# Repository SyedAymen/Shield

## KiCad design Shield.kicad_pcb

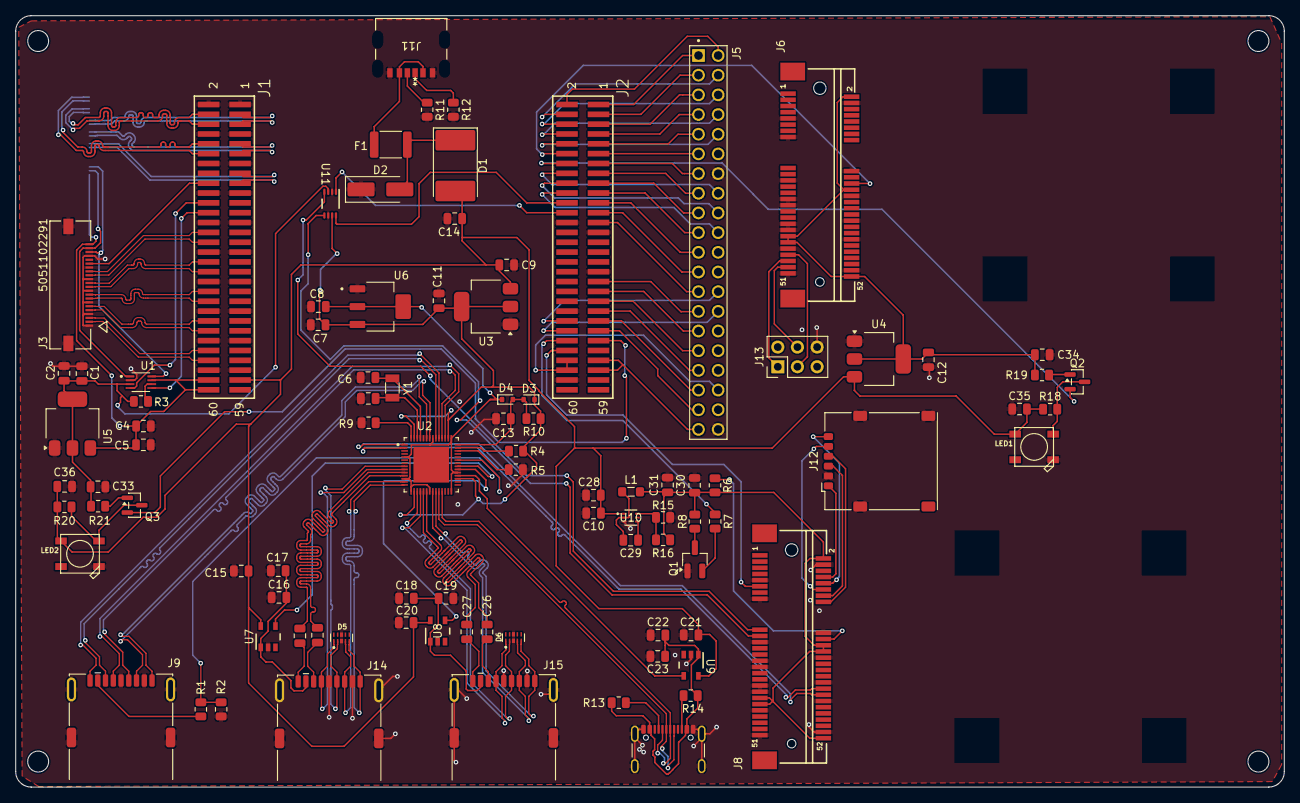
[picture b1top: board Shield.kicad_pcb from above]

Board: 4 copper layers, 163.7 x 99.6 mm, 94 parts (1 on the bottom side), 138 nets.

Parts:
C1, C4: 4.7 u; C_0805_2012Metric
C2, C5, C13, C15, C16, C18, C20, C21, C22, C24, C25, C26, C27, C29, C33, C34, C35, C36: 0.1 u; C_0805_2012Metric
C3, C6: 22 p; C_0805_2012Metric
C7, C9, C10, C14, C28: 10 u; C_0805_2012Metric
C8, C11, C12, C30, C31: 22 u; C_0805_2012Metric
C17, C19, C23: 100 u; C_0805_2012Metric
D1: D_Schottky; D_3220_8050Metric_Pad2.65x5.15mm_HandSolder
D2: D_TVS; D_SMA_Handsoldering
D3, D4: 1N4148WT; D_SOD-523
D5, D6: TPD4E02B04DQAR; DIO_TPD4E02B04DQAR
F1: Polyfuse; Fuse_1812_4532Metric
J1, J2: SAMTEC-FTS-130-01-X-DV
J3, J4: 5051102291; CON_5051102291_MOL
J5: 77313-118-40LF; AMPHENOL_77313-118-40LF
J6, J8: Bus_PCI_Express_Mini; TE_1775862-2
J7: USB_C_Receptacle; USB_C_Receptacle_GCT_USB4105-xx-A_16P_TopMnt_Horizontal
J9, J14, J15: USB3_A; USB_A_Receptacle_XKB_U231-091N-4BLRA00-S
J11: USB_C_Receptacle_PowerOnly_6P; U262-061N-4BVC10_XKB
J12: SIM_Card_Shielded; nanoSIM_Hinged_CUI_NSIM-2-C
J13: Conn_02x03_Odd_Even; PinHeader_2x03_P2.54mm_Vertical
L1: 3.3 uH; L_0805_2012Metric_Pad1.05x1.20mm_HandSolder
LED1, LED2: WS2812B
Q1: 2N3904; SOT-23_Handsoldering
Q2, Q3: MMBT3904; SOT-23
R1, R2, R6: 100 K; R_0805_2012Metric
R3, R7, R8, R15: 10 K; R_0805_2012Metric
R4: 200 K; R_0805_2012Metric
R5: 10; R_0805_2012Metric
R9, R10: 12 K; R_0805_2012Metric
R11, R12: 5.1 K; R_0805_2012Metric
R13, R14: 56 K; R_0805_2012Metric
R16: 33 K; R_0805_2012Metric
R18, R20, R21: 1 K; R_0805_2012Metric
R19: 2.2 K; R_0805_2012Metric
U1: TCA9406DCUR; SOP50P310X90-8N
U2: USB5744_2G; QFN40P700X700X100-57N
U3, U4: AMS1117-3.3; SOT-223-3_TabPin2
U5: AMS1117-1.8; SOT-223-3_TabPin2
U6: LM1117S-1.2; SOT230P695X180-4N
U7, U8, U9: TPS2051BDBVR; DBV0005A_N
U10: AP62300Z6-7; SOT563-Z6_1_DIO
U11: TXB0102DCUR; DCU0008A_N
Y1: Crystal; Crystal_SMD_3215-2Pin_3.2x1.5mm

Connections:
/1V8: C1.2, C2.2, C33.2, R3.1, R21.2, U1.3 (VCCA), U5.2 (VO), U11.3 (VCCA)
/3V3: C4.2, C5.2, J1.58, J1.60, J3.22, J4.22, U1.7 (VCCB), U5.3 (VI)
/3V3-VBUS-2: C12.2, C34.2, J6.2 (+3V3AUX), J6.24 (+3V3AUX), J6.39 (+3V3AUX), J6.41 (+3V3AUX), J6.52 (+3V3AUX), R19.1, U4.2 (VO)
/5V-VBUS: C9.2, C10.2, C14.2, C15.2, C20.2, C21.2, C28.2, C35.2, C36.2, D1.2 (A), J1.57, LED1.1-VDD (VDD), LED2.1-VDD (VDD), R18.1, R20.2, U3.3 (VI), U4.3 (VI), U7.5 (IN), U8.5 (IN), U9.5 (IN), U10.1 (VIN)
/5V-VBUS-PRT-2: C16.2, C17.2, J14.1 (VBUS), U7.1 (OUT)
/5V-VBUS-PRT-3: C18.2, C19.2, J15.1 (VBUS), U8.1 (OUT)
/5V-VBUS-PRT-4: C22.2, C23.2, J7.A4 (VBUS), J7.A9 (VBUS), J7.B4 (VBUS), J7.B9 (VBUS), R13.1, R14.1, U9.1 (OUT)
/CAM_EN: J1.18, J3.17
/CSI_CK+: J1.40, J3.9
/CSI_CK-: J1.42, J3.8
/CSI_D0+: J1.52, J3.3
/CSI_D0-: J1.54, J3.2
/CSI_D1+: J1.46, J3.6
/CSI_D1-: J1.48, J3.5
/CSI_D2+: J1.34, J3.12
/CSI_D2-: J1.36, J3.11
/CSI_D3+: J1.28, J3.15
/CSI_D3-: J1.30, J3.14
/DN2_D+: D5.2 (IO2), J14.3 (D+), U2.8 (USB2DN_DP2/PRT_DIS_P2)
/DN2_D-: D5.1 (IO1), J14.2 (D-), U2.9 (USB2DN_DM2/PRT_DIS_M2)
/DN2_RX+: D5.4 (IO3), J14.6 (SSRX+), U2.13 (USB3DN_RXDP2)
/DN2_RX-: D5.5 (IO4), J14.5 (SSRX-), U2.14 (USB3DN_RXDM2)
/DN2_TX1+: C25.2, J14.8 (SSTX-)
/DN2_TX1-: C24.2, J14.9 (SSTX+)
/DN2_TX+: C24.1, U2.10 (USB3DN_TXDP2)
/DN2_TX-: C25.1, U2.11 (USB3DN_TXDM2)
/DN3_D+: D6.2 (IO2), J15.3 (D+), U2.17 (USB2DN_DP3/PRT_DIS_P3)
/DN3_D-: D6.1 (IO1), J15.2 (D-), U2.18 (USB2DN_DM3/PRT_DIS_M3)
/DN3_RX+: D6.4 (IO3), J15.6 (SSRX+), U2.22 (USB3DN_RXDP3)
/DN3_RX-: D6.5 (IO4), J15.5 (SSRX-), U2.23 (USB3DN_RXDM3)
/DN3_TX1+: C26.2, J15.8 (SSTX-)
/DN3_TX1-: C27.2, J15.9 (SSTX+)
/DN3_TX+: C27.1, U2.19 (USB3DN_TXDP3)
/DN3_TX-: C26.1, U2.20 (USB3DN_TXDM3)
/DN4_D+: J7.A6 (D+), J7.B6 (D+), U2.24 (USB2DN_DP4/PRT_DIS_P4)
/DN4_D-: J7.A7 (D-), J7.B7 (D-), U2.25 (USB2DN_DM4/PRT_DIS_M4)
/DSI_CK+: J1.5, J4.9
/DSI_CK-: J1.3, J4.8
/DSI_D0+: J1.10, J4.3
/DSI_D0-: J1.12, J4.2
/DSI_D1+: J1.4, J4.6
/DSI_D1-: J1.6, J4.5
/DSI_D2+: J1.11, J4.12
/DSI_D2-: J1.9, J4.11
/DSI_D3+: J1.17, J4.15
/DSI_D3-: J1.15, J4.14
/JOUT_3V3: J2.53, J2.55, J5.39
/JOUT_5V: J2.54, J2.56, J5.36
/LR_MISO: J6.47 (Reserved), J13.1
/LR_MOSI: J6.49 (Reserved), J13.4
/LR_SCK: J6.45 (Reserved), J13.3
/LTE_D+: J8.38 (USB_D+), U2.1 (USB2DN_DP1/PRT_DIS_P1)
/LTE_D-: J8.36 (USB_D-), U2.2 (USB2DN_DM1/PRT_DIS_M1)
/LTE_UART_RXD: J8.19 (UIM_C4), U11.5 (A1)
/LTE_UART_TXD: J8.17 (UIM_C8), U11.4 (A2)
/MCU_CRS_SYNC / PA10: J2.25, J5.25
/MCU_I2C4_SCL / PF14: J2.16, J5.16
/MCU_I2C4_SDA / PF15: J2.18, J5.18
/MCU_MCO / PA8: J2.23, J5.23
/MCU_OPAMP1_VOUT / PA3: J2.20, J5.20
/MCU_PA0 UART4_TX AF8: J2.22, U11.8 (B1)
/MCU_PA1 UART4_RX AF8: J2.24, U11.1 (B2)
/MCU_PE7_LR: J2.12, J6.22 (~PERST)
/MCU_PE8_LED: J2.14, Q2.2 (E)
/MCU_PSSI_D0 / PC6: J2.1, J5.01
/MCU_PSSI_D1 / PC7: J2.3, J5.03
/MCU_PSSI_D2 / PC8: J2.5, J5.05
/MCU_PSSI_D3 / PC9: J2.7, J5.07
/MCU_PSSI_D4 / PE4: J2.9, J5.09
/MCU_PSSI_D5 / PI4: J2.11, J5.11
/MCU_PSSI_D6 / PI6: J2.13, J5.13
/MCU_PSSI_D7 / PI7: J2.15, J5.15
/MCU_PSSI_DE / PD8: J2.21, J5.21
/MCU_PSSI_PDCK / PD9: J2.17, J5.17
/MCU_PSSI_RDY / PI5: J2.19, J5.19
/MCU_SDMMC1_CMD / PD2: J2.2, J5.02
/MCU_TRACE_CLK / PE2: J2.4, J5.04
/MCU_TRACE_D0 / PE3: J2.6, J5.06
/MCU_TRACE_D2 / PE5: J2.8, J5.08
/MCU_TRACE_D3 / PE6: J2.10, J5.10
/PRT_CTL2: U2.35 (PRT_CTL2), U7.4 (EN)
/PRT_CTL3: U2.34 (PRT_CTL3), U8.4 (EN)
/PRT_CTL4: U2.32 (PRT_CTL4/GANG_PWR), U9.4 (EN)
/RST: C13.2, D3.2 (A), D4.2 (A), R10.2, U2.42 (RESET_N)
/SCL: J1.24, U1.5 (SCL_A)
/SCL1: J3.20, J4.20, U1.8 (SCL_B)
/SDA: J1.22, U1.4 (SDA_A)
/SDA1: J3.21, J4.21, U1.1 (SDA_B)
/SIM_CLK: J8.12 (UIM_CLK), J12.3 (CLK)
/SIM_DT: J8.10 (UIM_DATA), J12.7 (I/O)
/SIM_RST: J8.14 (~UIM_RESET), J12.2 (RST)
/SIM_VCC: J8.8 (UIM_PWR), J12.1 (VCC)
/SIM_VPP: J8.16 (UIM_VPP), J12.6 (VPP)
/SOC_GPIO_0_SE0: J2.37, J5.27
/SOC_GPIO_1_SEO: J2.39, J5.29
/SOC_GPIO_2_SEO: J2.41, J5.31
/SOC_GPIO_3_SEO: J2.43, J5.33
/SOC_GPIO_18_PWM_LED: J2.49, Q3.2 (E)
/SOC_GPIO_82_SEO: J2.47, J5.37
/SOC_GPIO_86_SEO: J2.45, J5.35
/SOC_GPIO_98: J2.46, J5.26
/SOC_GPIO_99: J2.48, J5.28
/SOC_GPIO_100_PRST_LTE: J2.50, R7.2
/SOC_GPIO_101_PPS: J2.52, J8.11 (REFCLK-)
/UP_D+: J9.3 (D+), U2.46 (USB2UP_DM)
/UP_D-: J9.2 (D-), U2.45 (USB2UP_DP)
/UP_RX+: J9.6 (SSRX+), U2.50 (USB3UP_RXDP)
/UP_RX-: J9.5 (SSRX-), U2.51 (USB3UP_RXDM)
/UP_TX+: J9.9 (SSTX+), U2.47 (USB3UP_TXDP)
/UP_TX-: J9.8 (SSTX-), U2.48 (USB3UP_TXDM)
/UP_VBUS: R1.1, R2.2, U2.37 (VBUS_DET/GPIO16)
/VBUCK: C30.2, C31.2, J8.2 (+3V3AUX), J8.22 (~PERST), J8.24 (+3V3AUX), J8.39 (+3V3AUX), J8.41 (+3V3AUX), J8.52 (+3V3AUX), L1.2, R6.2, R8.2, R16.2
GND: C1.1, C2.1, C3.1, C4.1, C5.1, C6.1, C7.1, C8.1, C9.1, C10.1, C11.1, C12.1, C13.1, C14.1, C15.1, C16.1, C17.1, C18.1, C19.1, C20.1, C21.1, C22.1, C23.1, C28.1, C30.1, C31.1, C33.1, C34.1, C35.1, C36.1, D2.1 (A1), D5.3 (GND), D5.8 (GND), D6.3 (GND), D6.8 (GND), J1.1, J1.2, J1.7, J1.8, J1.13, J1.14, J1.19, J1.20, J1.25, J1.26, J1.31, J1.32, J1.37, J1.38, J1.43, J1.44, J1.49, J1.50, J1.55, J1.56, J2.26, J2.27, J2.35, J2.44, J2.58, J3.1, J3.4, J3.7, J3.10, J3.13, J3.16, J3.19, J3.P1, J3.P2, J4.1, J4.4, J4.7, J4.10, J4.13, J4.16, J4.P1, J4.P2, J5.14, J5.40, J6.4 (GND), J6.9 (GND), J6.15 (GND), J6.18 (GND), J6.21 (GND), J6.26 (GND), J6.27 (GND), J6.29 (GND), J6.34 (GND), J6.35 (GND), J6.37 (GND), J6.40 (GND), J6.43 (GND), J6.50 (GND), J6.51 (Reserved), J7.A1 (GND), J7.A12 (GND), J7.B1 (GND), J7.B12 (GND), J7.S1 (SHIELD), J8.4 (GND), J8.9 (GND), J8.15 (GND), J8.18 (GND), J8.21 (GND), J8.26 (GND), J8.27 (GND), J8.29 (GND), J8.34 (GND), J8.35 (GND), J8.37 (GND), J8.40 (GND), J8.43 (GND), J8.50 (GND), J8.51 (Reserved), J9.4 (GND), J9.7 (DRAIN), J9.10 (SHIELD), J11.A12 (GND), J11.B12 (GND), J12.5 (GND), J12.SH, J13.6, J14.4 (GND), J14.7 (DRAIN), J14.10 (SHIELD), J15.4 (GND), J15.7 (DRAIN), J15.10 (SHIELD), LED1.3-GND (GND), LED2.3-GND (GND), Q1.1 (E), R2.1, R5.1, R9.1, R11.1, R12.1, R15.1, U1.2 (GND), U3.1 (GND), U4.1 (GND), U5.1 (GND), U6.1 (GND), U7.2 (GND), U8.2 (GND), U9.2 (GND), U10.3 (GND), U11.2 (GND), U11.6 (OE)
unnamed: D1.1 (K), D2.2 (A2), F1.1
unnamed: F1.2, J11.A9 (VBUS), J11.B9 (VBUS)
unnamed: J7.A5 (CC1), R13.2
unnamed: J7.B5 (CC2), R14.2
unnamed: J8.20 (~W_DISABLE), R6.1
unnamed: J9.1 (VBUS), R1.2
unnamed: J11.A5 (CC1), R12.2
unnamed: J11.B5 (CC2), R11.2
unnamed: LED1.4-DIN (DI), Q2.3 (C), R18.2
unnamed: LED2.4-DIN (DI), Q3.3 (C), R20.1
unnamed: Q1.2 (B), R7.1
unnamed: Q1.3 (C), R8.1
unnamed: Q2.1 (B), R19.2
unnamed: Q3.1 (B), R21.1
unnamed: R3.2, U1.6 (OE)
unnamed: R9.2, U2.56 (RBIAS)
unnamed: R4.1, U2.41 (SPI_CE_N/CFG_NON_REM/GPIO7)
unnamed: R5.2, U2.40 (SPI_DI/CFG_BC_EN/GPIO9)
unnamed: C3.2, U2.54 (XTALI/CLK_IN), Y1.1
unnamed: C6.2, U2.53 (XTALO), Y1.2
unnamed: C29.2, U10.4 (BST)
unnamed: R15.2, R16.1, U10.6 (FB)
unnamed: C29.1, L1.1, U10.2 (SW)
VDD12: C8.2, D4.1 (K), U2.5 (VDD12), U2.12 (VDD12), U2.15 (VDD12), U2.21 (VDD12), U2.28 (VDD12), U2.33 (VDD12), U2.43 (VDD12), U2.49 (VDD12), U6.2 (VOUT), U6.4 (VOUT)
VDD33: C7.2, C11.2, D3.1 (K), R4.2, R10.1, U2.16 (VDD33), U2.31 (VDD33), U2.44 (VDD33), U2.55 (VDD33), U3.2 (VO), U6.3 (VIN), U11.7 (VCCB)
